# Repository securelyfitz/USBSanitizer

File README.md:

USB Sanitizer
================

A small and cheap standalone USB drive wiper

The code is based heavily on the USBHostGeneric example from FTDI as well as USB-Writeblocker by Phil Polstra

View 'slides' from hushcon:
https://rawgit.com/securelyfitz/USBSanitizer/master/Hushcon%20East/Hushcon%20East%20-%20USBSanitizer%20presentation.html#/overview

Disclaimer:
-----------
USB sanitizer has some issues with a large number of USB drives right now. I should have an update shortly once i properly probe the SCSI device status/ready commands before writing...

Overview
---------
USB has issues, and being a very layered architecture, has layers of issues.

I deal with distributing class material on USB drives at security conferences, and prefer to reuse drives. At first i had a standalone air-gapped PC that did the job automatically when a drive was inserted, and more recently i have used a pogoplug modified for the purpose. This is overkill, and it's also not any guarantee that my air-gapped system that never gets any updates isn't vulnerable  to layers of potentially exploitable bugs.

After seeing how USB drives are used to transport information to air-gapped computers and learning that many securedrop sites use USB drives to transfer data to air-gapped computers, i realized that there is a broader use for a simple, standalone USB drive wiper.

Objective
---------
I aimed for a device that was:
- small (no larger than a usb drive itself)
- cheap ($5-10 BOM)
- bare metal (little or no OS)
- easy to build (Leaded SMT, single chip if possible)
- easy to code (cause i am teh suk at codez)
- easy to program ($50 programmer for a $5 board is lame)
 
Hardware
--------
- The main IC is the FTDI VNC2 which has a proprietary harvard architecture, proprietary 'RTOS', built in flash, and built in usb host capability. No other chip that i found under $10 had all that on a single chip.
- The board is 2.5x5cm. In addition to the VNC2, there is a single voltage regulator, a resonator, and a bunch of passive devices.
- Power is provided by the USB Male connector. Data pins are not connected to this connector in a normal build. If connected, this device can also be used with Phil Polstra's USB-Writeblocker: https://github.com/ppolstra/USB-Writeblocker
- A USB Female connector receives the flash drive (or even usb hdd/ssd).
- There is a 9 pin header for programming that can be unpopulated for production devices. Programming can be done via standard UART with hardware flow control.

Software
--------
FTDI provides an IDE and compiler for the VNC2 for windows only. It didn't run well on WINE on my initial attempts. The IDE can only be downloaded from them, without SSL. FTDI doesn't provide hashes of the executables either. If you're lucky enough to get the same embedded malware as me, your MD5s should be:
- http://www.ftdichip.com/Firmware/vnc2toolchain/Vinculum%20II%20Installer%20V2.0.0-SP1.exe
7b60bdc4313ed0449374dcaab23e0e84 
- http://www.ftdichip.com/Support/Utilities/VPROG.zip
ab5ec25792ef7a4f780aa507cd326ba5 
- http://www.ftdichip.com/Support/Utilities/FT_Prog_v3.0.60.276%20Installer.zip
f9a62778065ca541005dd138a52c5c99

FTDI provides an API for doing some basic USB stuff. They've got APIs to navigate filesystems and play audio files, but they're missing the ability to do basic things like query the capacity of a block storage device. Because of this i basically wrote everything at the raw USB level. I let the FTDI library take care of ACKs and NAKs but otherwise do most of the data transfer myself.

Everything about the VINCULUM is flakey - the IDE, the compiler, the hardware, the architecture in general. In retrospect there are probably more exploitable bugs in this bare-bones embedded device than there were in my air-gapped PC.

PCB Files
---------
* .sch and .brd: eagle schematic and board files 
* .lbr: eagle libraries for board outline and text items 
* .G* and .TXT: gerber files for fabricating board

Building:
------------------
See a video of building up a prototype. V1.0 is essentially the same, with the addition of a reset switch.

https://www.youtube.com/watch?v=V60TksZd7uk

Bill of Materials for ordering at digikey is in [USBSanitizer.csv]. Cost is $8.60 for a single set.

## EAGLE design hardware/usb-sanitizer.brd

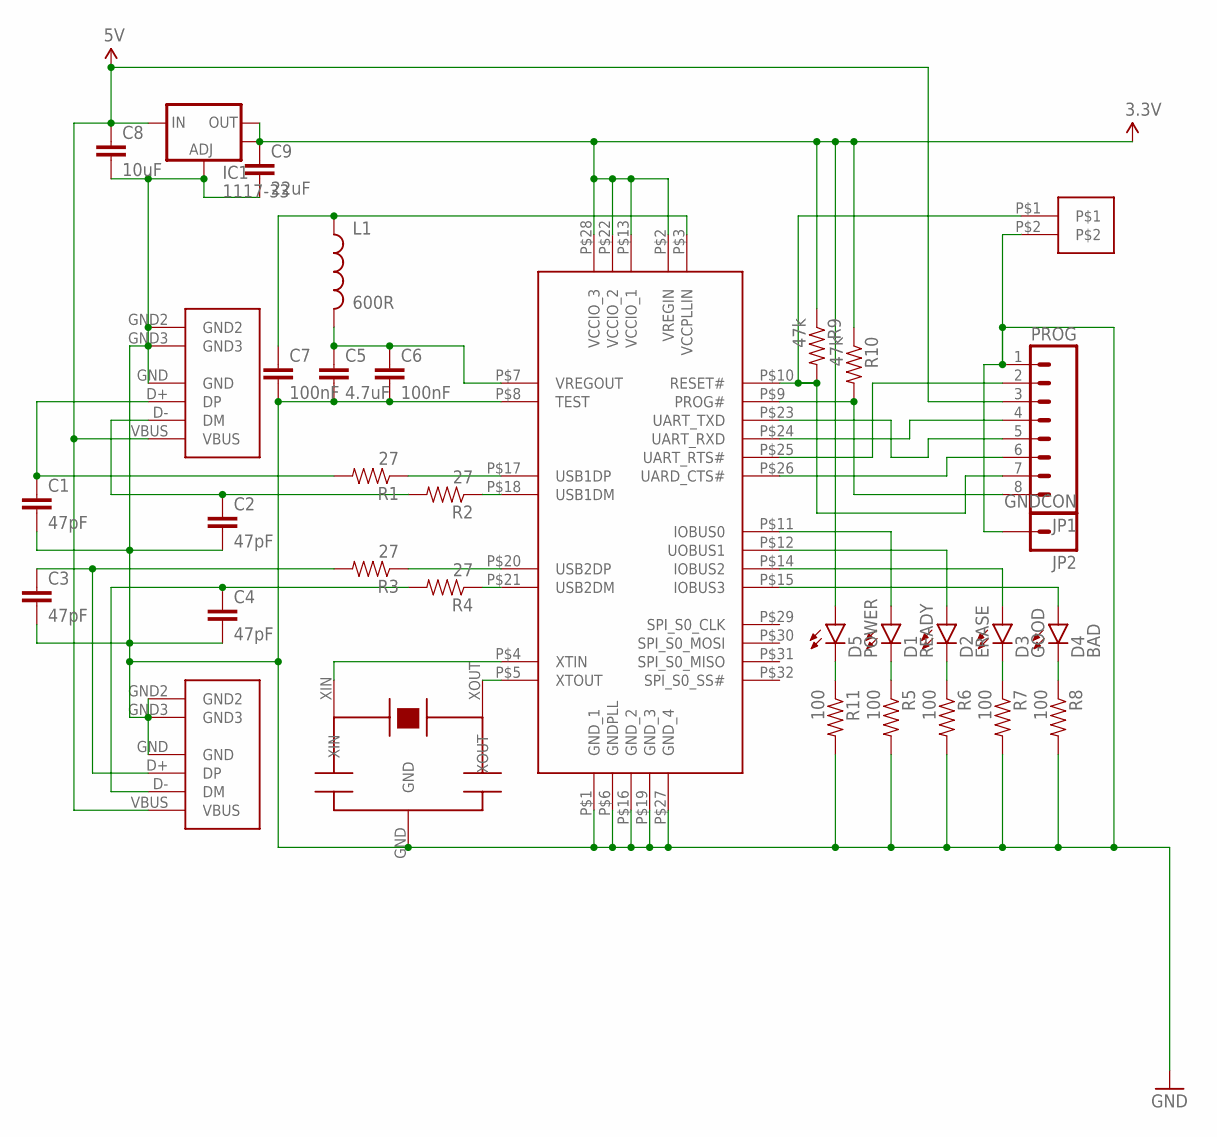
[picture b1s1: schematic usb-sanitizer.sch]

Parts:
C1, C2, C3, C4: 47pF; 0805
C5: 4.7uF; 0805
C6, C7: 100nF; 0805
C8: 10uF; 0805
C9: 22uF; 0805
D1: READY; 0805
D2: ERASE; 0805
D3: GOOD; 0805
D4: BAD; 0805
D5: POWER; 0805
IC1: 1117-33; SOT223
JP1: PROG; 1X08_LOCK
JP2: GNDCON; 1X01
L1: 600R; 0805
R1, R2, R3, R4: 27; 0805
R5, R6, R7, R8, R11: 100; 0805
R9, R10: 47k; 0805
U$1: VNC2; QFP32
U$4: RESONATOR
U$5: SWITCH
USB_FEMALE: USB_AF; USB-A-F
USB_MALE: USB_AM; USB-A-M

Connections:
3.3V: C9.1, D5.1 (A), IC1.2 (OUT), IC1.4 (OUT), R9.1, R10.1, U$1.P$2 (VREGIN), U$1.P$13 (VCCIO_1), U$1.P$22 (VCCIO_2), U$1.P$28 (VCCIO_3)
5V: C8.1, IC1.3 (IN), JP1.3, USB_FEMALE.VBUS, USB_MALE.VBUS
GND: C1.2, C2.2, C3.2, C4.2, C5.2, C6.2, C7.2, C8.2, C9.2, IC1.1 (ADJ), JP1.1, JP2.1, R5.2, R6.2, R7.2, R8.2, R11.2, U$1.P$1 (GND_1), U$1.P$6 (GNDPLL), U$1.P$8 (TEST), U$1.P$16 (GND_2), U$1.P$19 (GND_3), U$1.P$27 (GND_4), U$4.GND, U$5.P$2, USB_FEMALE.GND, USB_FEMALE.GND2, USB_FEMALE.GND3, USB_MALE.GND, USB_MALE.GND2, USB_MALE.GND3
unnamed: D5.2 (C), R11.1
unnamed: C5.1, C6.1, L1.2, U$1.P$7 (VREGOUT)
unnamed: C7.1, L1.1, U$1.P$3 (VCCPLLIN)
unnamed: U$1.P$5 (XTOUT), U$4.XOUT
unnamed: U$1.P$4 (XTIN), U$4.XIN
unnamed: JP1.2, U$1.P$25 (UART_RTS#)
unnamed: JP1.4, U$1.P$24 (UART_RXD)
unnamed: JP1.5, U$1.P$23 (UART_TXD)
unnamed: JP1.6, U$1.P$26 (UARD_CTS#)
unnamed: JP1.8, R10.2, U$1.P$9 (PROG#)
unnamed: JP1.7, R9.2, U$1.P$10 (RESET#), U$5.P$1
unnamed: D1.2 (C), R5.1
unnamed: D2.2 (C), R6.1
unnamed: D4.2 (C), R8.1
unnamed: D3.2 (C), R7.1
unnamed: D1.1 (A), U$1.P$11 (IOBUS0)
unnamed: D2.1 (A), U$1.P$12 (UOBUS1)
unnamed: D3.1 (A), U$1.P$14 (IOBUS2)
unnamed: D4.1 (A), U$1.P$15 (IOBUS3)
USB1DM: R2.1, U$1.P$18 (USB1DM)
USB1DP: R1.1, U$1.P$17 (USB1DP)
USB1RDM: C2.1, R2.2, USB_FEMALE.D- (DM)
USB1RDP: C1.1, R1.2, USB_FEMALE.D+ (DP)
USB2DM: R4.1, U$1.P$21 (USB2DM)
USB2DP: R3.1, U$1.P$20 (USB2DP)
USB2RDM: C4.1, R4.2, USB_MALE.D- (DM)
USB2RDP: C3.1, R3.2, USB_MALE.D+ (DP)

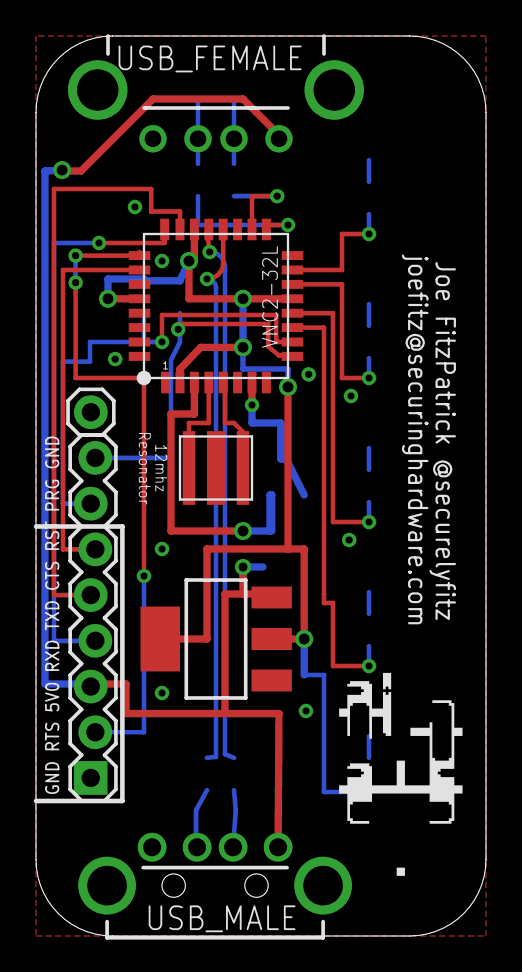
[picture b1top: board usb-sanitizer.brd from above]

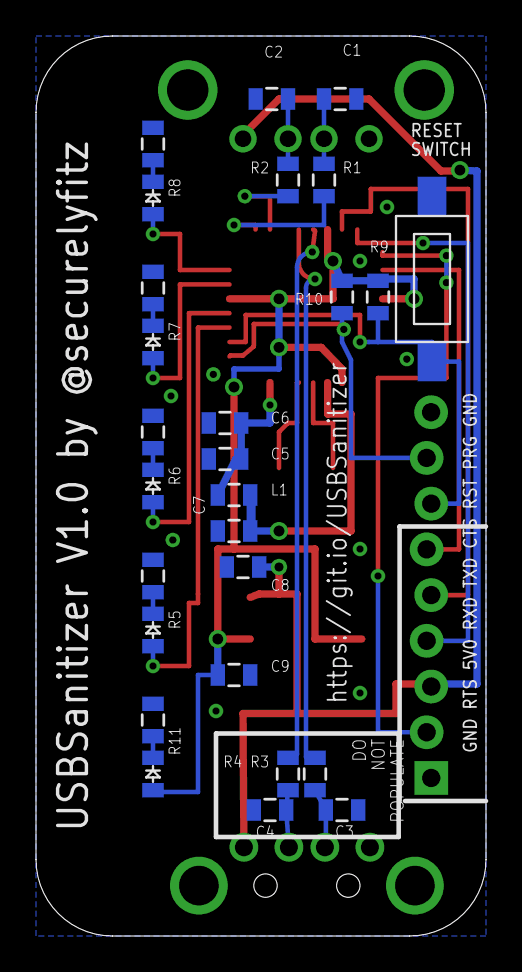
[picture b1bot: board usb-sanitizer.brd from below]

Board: 2 copper layers, 25.0 x 50.0 mm, 36 parts (27 on the bottom side), 30 nets.

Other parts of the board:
U$2: SH-HALFINCH
U$3: OSHW

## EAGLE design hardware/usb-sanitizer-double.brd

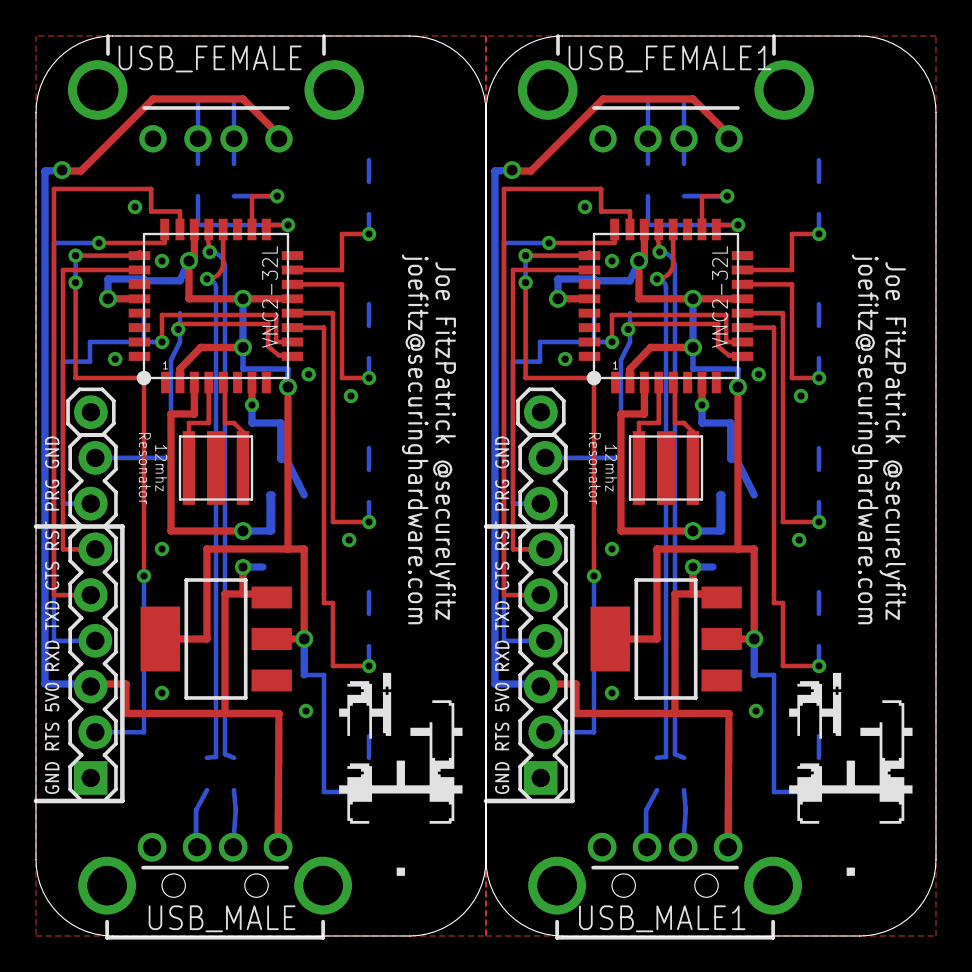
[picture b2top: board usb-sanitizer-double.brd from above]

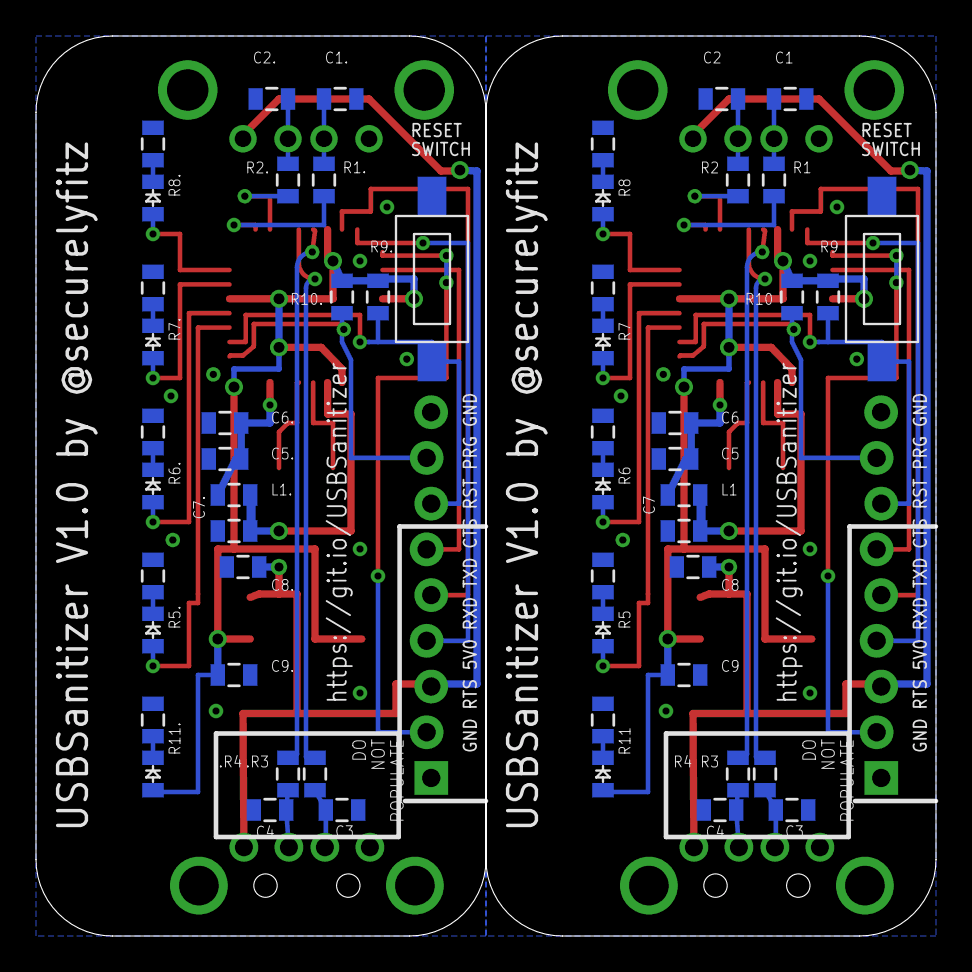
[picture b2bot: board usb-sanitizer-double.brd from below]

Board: 2 copper layers, 50.0 x 50.0 mm, 72 parts (54 on the bottom side), 60 nets.

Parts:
.C3, .C4: 47pF; 0805
.R3, .R4: 27; 0805
C1, C1., C2, C2., C3, C4: 47pF; 0805
C5, C5.: 4.7uF; 0805
C6, C6., C7, C7.: 100nF; 0805
C8, C8.: 10uF; 0805
C9, C9.: 22uF; 0805
D1, D6: READY; 0805
D2, D7: ERASE; 0805
D3, D8: GOOD; 0805
D4, D9: BAD; 0805
D5, D10: POWER; 0805
IC1, IC2: 1117-33; SOT223
JP1, JP3: PROG; 1X08_LOCK
JP2, JP4: GNDCON; 1X01
L1, L1.: 600R; 0805
R1, R1., R2, R2., R3, R4: 27; 0805
R5, R5., R6, R6., R7, R7., R8, R8., R11, R11.: 100; 0805
R9, R9., R10, R10.: 47k; 0805
U$1, U$6: VNC2; QFP32
U$2, U$8: SH-HALFINCH
U$3, U$9: OSHW
U$4, U$7: RESONATOR
U$5, U$10: SWITCH
USB_FEMALE, USB_FEMALE1: USB_AF; USB-A-F
USB_MALE, USB_MALE1: USB_AM; USB-A-M

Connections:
3.3V: C9.1, D5.1, IC1.2, IC1.4, R9.1, R10.1, U$1.P$2, U$1.P$13, U$1.P$22, U$1.P$28
3.3V1: C9..1, D10.1, IC2.2, IC2.4, R9..1, R10..1, U$6.P$2, U$6.P$13, U$6.P$22, U$6.P$28
5V: C8.1, IC1.3, JP1.3, USB_FEMALE.VBUS, USB_MALE.VBUS
5V1: C8..1, IC2.3, JP3.3, USB_FEMALE1.VBUS, USB_MALE1.VBUS
GND: C1.2, C2.2, C3.2, C4.2, C5.2, C6.2, C7.2, C8.2, C9.2, IC1.1, JP1.1, JP2.1, R5.2, R6.2, R7.2, R8.2, R11.2, U$1.P$1, U$1.P$6, U$1.P$8, U$1.P$16, U$1.P$19, U$1.P$27, U$4.GND, U$5.P$2, USB_FEMALE.GND, USB_FEMALE.GND2, USB_FEMALE.GND3, USB_MALE.GND, USB_MALE.GND2, USB_MALE.GND3
GND1: .C3.2, .C4.2, C1..2, C2..2, C5..2, C6..2, C7..2, C8..2, C9..2, IC2.1, JP3.1, JP4.1, R5..2, R6..2, R7..2, R8..2, R11..2, U$6.P$1, U$6.P$6, U$6.P$8, U$6.P$16, U$6.P$19, U$6.P$27, U$7.GND, U$10.P$2, USB_FEMALE1.GND, USB_FEMALE1.GND2, USB_FEMALE1.GND3, USB_MALE1.GND, USB_MALE1.GND2, USB_MALE1.GND3
unnamed: C5..1, C6..1, L1..2, U$6.P$7
unnamed: C7..1, L1..1, U$6.P$3
unnamed: U$6.P$5, U$7.XOUT
unnamed: U$6.P$4, U$7.XIN
unnamed: JP3.2, U$6.P$25
unnamed: JP3.4, U$6.P$24
unnamed: JP3.5, U$6.P$23
unnamed: JP3.6, U$6.P$26
unnamed: D5.2, R11.1
unnamed: C5.1, C6.1, L1.2, U$1.P$7
unnamed: C7.1, L1.1, U$1.P$3
unnamed: JP3.8, R10..2, U$6.P$9
unnamed: U$1.P$5, U$4.XOUT
unnamed: U$1.P$4, U$4.XIN
unnamed: JP1.2, U$1.P$25
unnamed: JP1.4, U$1.P$24
unnamed: JP1.5, U$1.P$23
unnamed: JP1.6, U$1.P$26
unnamed: JP3.7, R9..2, U$6.P$10, U$10.P$1
unnamed: JP1.8, R10.2, U$1.P$9
unnamed: JP1.7, R9.2, U$1.P$10, U$5.P$1
unnamed: D1.2, R5.1
unnamed: D2.2, R6.1
unnamed: D4.2, R8.1
unnamed: D3.2, R7.1
unnamed: D1.1, U$1.P$11
unnamed: D2.1, U$1.P$12
unnamed: D3.1, U$1.P$14
unnamed: D4.1, U$1.P$15
unnamed: D6.2, R5..1
unnamed: D7.2, R6..1
unnamed: D9.2, R8..1
unnamed: D8.2, R7..1
unnamed: D6.1, U$6.P$11
unnamed: D7.1, U$6.P$12
unnamed: D8.1, U$6.P$14
unnamed: D9.1, U$6.P$15
unnamed: D10.2, R11..1
USB1DM: R2.1, U$1.P$18
USB1DM1: R2..1, U$6.P$18
USB1DP: R1.1, U$1.P$17
USB1DP1: R1..1, U$6.P$17
USB1RDM: C2.1, R2.2, USB_FEMALE.D-
USB1RDM1: C2..1, R2..2, USB_FEMALE1.D-
USB1RDP: C1.1, R1.2, USB_FEMALE.D+
USB1RDP1: C1..1, R1..2, USB_FEMALE1.D+
USB2DM: R4.1, U$1.P$21
USB2DM1: .R4.1, U$6.P$21
USB2DP: R3.1, U$1.P$20
USB2DP1: .R3.1, U$6.P$20
USB2RDM: C4.1, R4.2, USB_MALE.D-
USB2RDM1: .C4.1, .R4.2, USB_MALE1.D-
USB2RDP: C3.1, R3.2, USB_MALE.D+
USB2RDP1: .C3.1, .R3.2, USB_MALE1.D+

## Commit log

2015-04-30 initial commit. Eagle board files, vinculum IDE files, and source files.
2015-04-30 adding readme and BOM:
2015-05-02 posting 'slides' from hushcon east
2015-05-02 link to presentation and stuff
2021-03-05 Update README.md
    Minor typo fixes

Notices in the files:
parts and their libraries:
SparkFun-Passives: Licensing: Creative Commons ShareAlike 4.0 International - https://creativecommons.org/licenses/by-sa/4.0
